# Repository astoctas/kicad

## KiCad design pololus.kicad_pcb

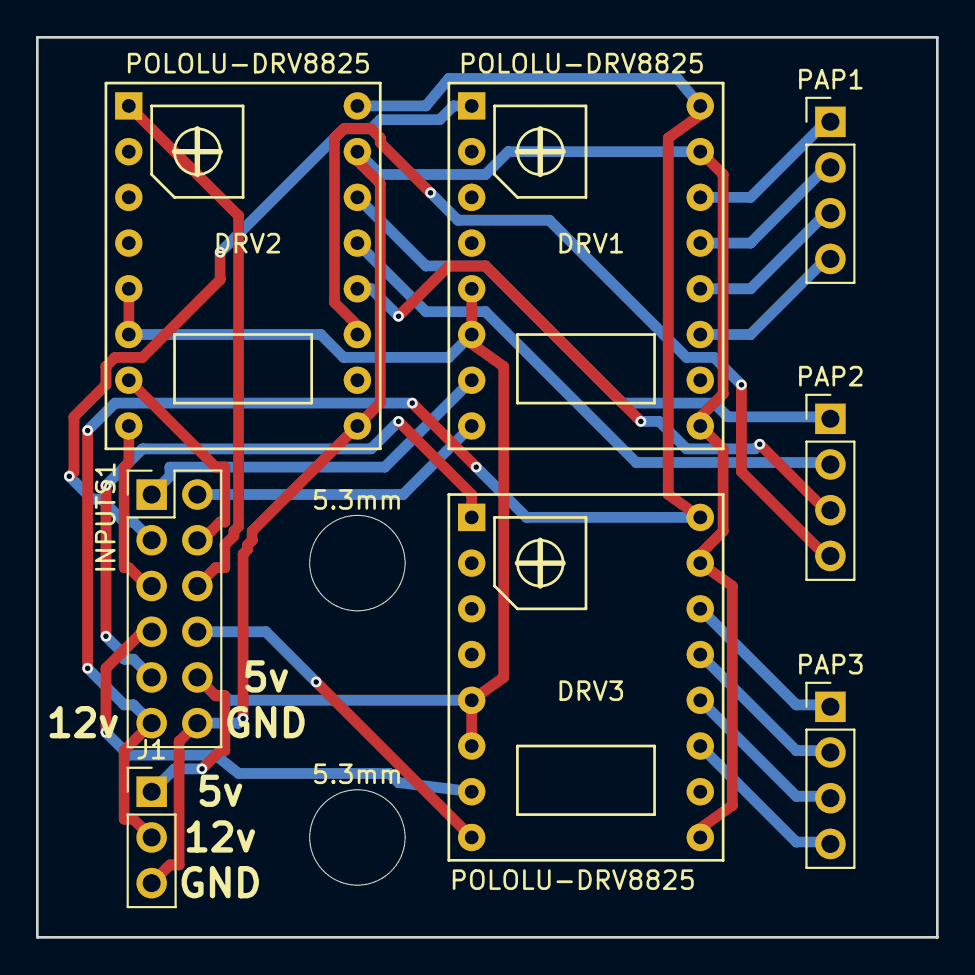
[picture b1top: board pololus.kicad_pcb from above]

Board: 2 copper layers, 50.0 x 50.0 mm, 10 parts (0 on the bottom side), 24 nets.

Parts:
5.3mm, 5.3mm#2: MountingHole_5.3mm_M5
DRV1, DRV2, DRV3: POLOLU-DRV8825
INPUTS1: Conn_02x06_Odd_Even; Pin_Header_Straight_2x06_Pitch2.54mm
J1: Conn_01x03; Pin_Header_Straight_1x03_Pitch2.54mm
PAP1, PAP2, PAP3: Conn_01x04; Pin_Header_Straight_1x04_Pitch2.54mm

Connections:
+5V: DRV1.5, DRV1.6, DRV2.5, DRV2.6, DRV3.5, DRV3.6, INPUTS1.10, J1.1
+12V: DRV1.16, DRV2.16, DRV3.16, INPUTS1.11, J1.2
GND: DRV1.9, DRV1.15, DRV2.9, DRV2.15, DRV3.9, DRV3.15, INPUTS1.12, J1.3
unnamed: DRV1.1, INPUTS1.3
unnamed: DRV1.7, INPUTS1.1
unnamed: DRV1.8, INPUTS1.2
unnamed: DRV1.11, PAP1.4
unnamed: DRV1.12, PAP1.3
unnamed: DRV1.13, PAP1.2
unnamed: DRV1.14, PAP1.1
unnamed: DRV2.1, INPUTS1.6
unnamed: DRV2.7, INPUTS1.4
unnamed: DRV2.8, INPUTS1.5
unnamed: DRV2.11, PAP2.4
unnamed: DRV2.12, PAP2.3
unnamed: DRV2.13, PAP2.2
unnamed: DRV2.14, PAP2.1
unnamed: DRV3.1, INPUTS1.9
unnamed: DRV3.7, INPUTS1.7
unnamed: DRV3.8, INPUTS1.8
unnamed: DRV3.11, PAP3.4
unnamed: DRV3.12, PAP3.3
unnamed: DRV3.13, PAP3.2
unnamed: DRV3.14, PAP3.1

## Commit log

2018-10-03 Dev pololus
2018-10-14 Release DLL
2018-10-18 Pololus
2018-10-18 Modificaciones
